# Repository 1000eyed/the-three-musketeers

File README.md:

# The three musketeers
A low(-ish) profile 3- or 4-row mechanical keyboard with a speaker supporting ortho and alpha stagger layouts, optional numpad, and optional 3 function keys.

## About

The three musketeers is a mechanical keyboard powered by RP2040 Zero development board. It is designed with optional clusters in mind, which you can either use or break away. Here are some particulars:

- Designed to support either KS-33B or Gateron low profile V3 switches. The PCB will accept the MX style switches too, but there is no case for these so far.
- I designed a couple of cases for this PCB, see below. All of them are low profile aimed on Gateron switches exclusively.
- Features KLJ-1102 speaker. I use it for announcing mod activation on keyboards with home row modifiers. You may use it for anything else per your liking, or not use it at all.
- Main cluster supports either ortho or alpha stagger layouts.
- There are multiple space row options, including 7U bar seesaw mount.
- No stabilizers!

## How to build one

> [!IMPORTANT]
> If you will be chopping the function column off the PCB, make sure this trace remains intact. Otherwise you will have to bridge it.
> 

#### Part list
| #     | name                 | comments                                  |
|-------|----------------------|-------------------------------------------|
| 1     | Main PCB             | Order at fabricator of your choice        |
| 1     | Case                 | See below                                 |
| 1     | RP2040 Zero          |                                           |
| 36-56 | Switches             | Gateron low profile KS-33b or v3          |
| 36-56 | Diodes               | SOD-123                                   |
| 36-56 | Keycaps              | MX-compatible                             |
| 4     | Rubber bump-ons      | 10mm                                      |
| 16    | Magnets              | Cylinder 1x5mm                            |
| 1     | Optional Speaker     | KLJ-1102 (https://keeb.supply/products/piezo-buzzer)  |

### 3D-printed cases

All these cases are printed in SLA by JLC. They turned out for me half-decent, and you may face warpage of longer parts. The assembly is straight-forward:

- Solder the sockets to the PCB and the pins to the controller.
- Solder the speaker of you have it.
- Mount the corner switches to the upper case part and solder them to the PCB. The PCB should seat flush to the integrated case.
- Mount and solder all other switches.
- Mount the controller onto the PCB.

Done!

### Concrete case

A successful attempt of a concrete case was made! I used MOBY DUR furniture concrete mixture, which turned out sturdy and was easy to demould, but required sanding (https://www.moertelshop.com/buy-white-grout-for-concrete-furniture-cheaply-5.html). You may or may not get better results with liquid floor mixtures.

The assembly consists of a concrete case and plate insert. The plate is soldered together with the PCB as with the 3D-printed cases, and then inserted into the case. It should be held inside firmly with friction.

- Print out the negative mould in PLA.
- Pour the concrete into the mold, make sure it sets level.
- When it sets, carefully demould with hot air gun. Try aiming at the mould rather than at the concrete directly.
- Repair any damage you made along the way.
- If you find this appealing, you same sand the case. Make sure not to sand the internal cavities!

### Aluminium case (handwire)

This version does not use the PCB at all, and thus is not directly connected to the The three musketeers project. However it was designed in the same wave of inspiration as everything else, so I figured it belongs here too. 

> [!NOTE]
> I used Kailh Element switches for this project. If you want to use different ones, check their plate footprint and adjust accordingly.

#### Part list
| #     | name                 | comments                                  |
|-------|----------------------|-------------------------------------------|
| 1     | Main case            | Order at fabricator of your choice        |
| 1     | Plate                | I printed out in PETG                     |
| 1     | MCU insert           | I printed out in PETG. Avoid brittle materials.                    |
| 1     | RP2040 Zero          |                                           |
| 36    | Switches             | Kailh Element                             |
| 36    | Diodes               |                                           |
| 36    | Keycaps              | MX-compatible                             |
| 4     | Rubber bump-ons      | 10mm                                      |
| 6     | M3 hex socket screws | 5 or 6 mm will do                               |
| 1     | Optional Speaker     | KLJ-1102 (https://keeb.supply/products/piezo-buzzer)  |

- Solder the switches to the plate with diodes like usual.
- Hook up the matrix to applicable pins on the controller.
- Clip in the controller into the controller insert.
- Clip the insert into the aluminim case.
- Screw the plate to the case while carefully laying out the wires. 

## Firmware

I don't provide firmware to this keyboard for now. For those wishing to compile their own, see the rows and columns references in the pcb schematic.

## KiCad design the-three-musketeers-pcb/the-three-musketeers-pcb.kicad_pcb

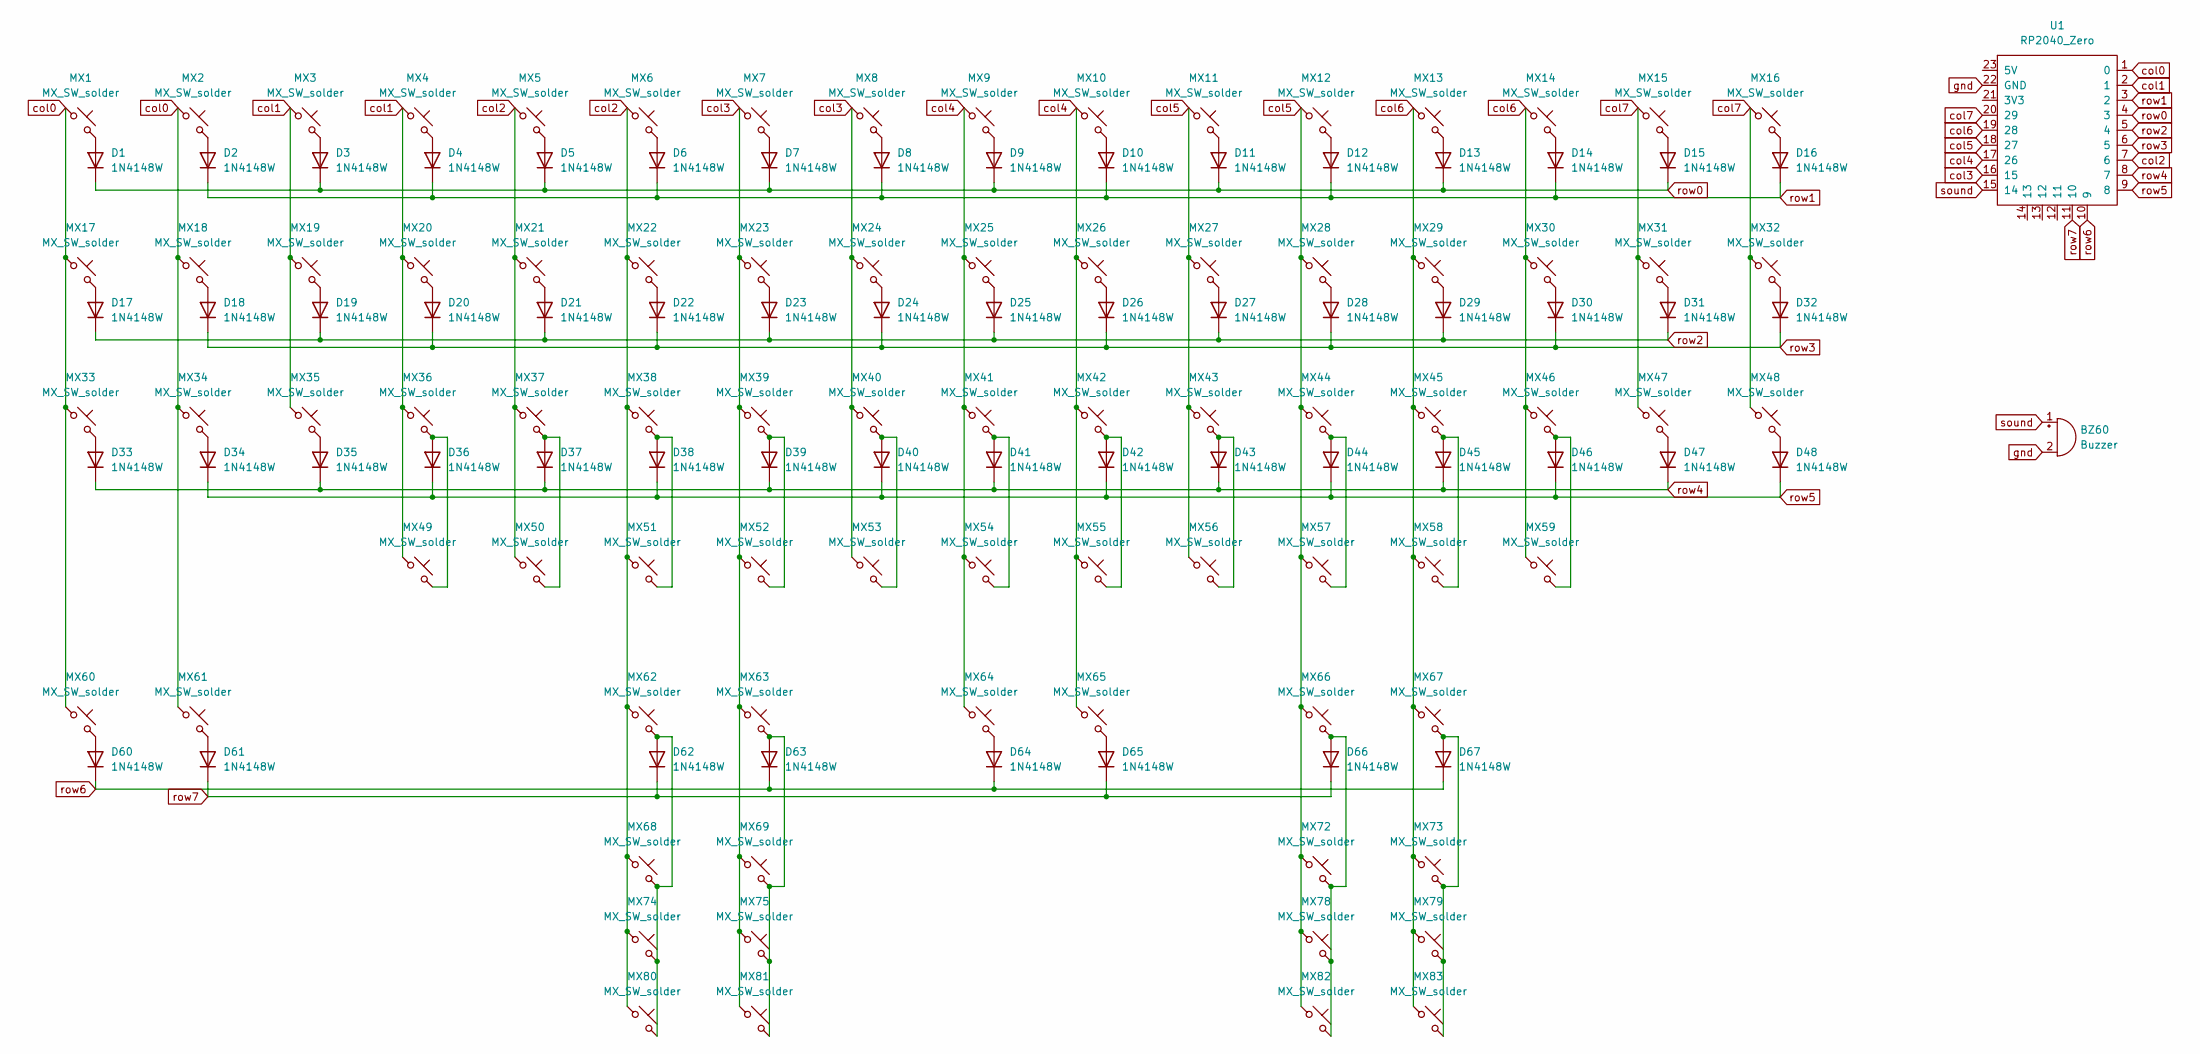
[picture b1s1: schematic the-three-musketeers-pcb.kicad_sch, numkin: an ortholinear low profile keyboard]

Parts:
BZ60: Buzzer; KLJ-1102
D1, D2, D3, D4, D5, D6, D7, D8, D9, D10, D11, D12, D13, D14, D15, D16, D17, D18, D19, D20, D21, D22, D23, D24, D25, D26, D27, D28, D29, D30, D31, D32, D33, D34, D35, D36, D37, D38, D39, D40, D41, D42, D43, D44, D45, D46, D47, D48, D60, D61, D62, D63, D64, D65, D66, D67: 1N4148W; Diode_SOD-123
MX1, MX2, MX3, MX4, MX5, MX6, MX7, MX8, MX9, MX10, MX11, MX12, MX13, MX14, MX15, MX16, MX17, MX18, MX19, MX20, MX21, MX22, MX23, MX24, MX25, MX26, MX27, MX28, MX29, MX30, MX31, MX32, MX33, MX34, MX35, MX36, MX37, MX38, MX39, MX40, MX41, MX42, MX43, MX44, MX45, MX46, MX47, MX48, MX49, MX50, MX51, MX52, MX53, MX54, MX55, MX56, MX57, MX58, MX59, MX60, MX61, MX62, MX63, MX64, MX65, MX66, MX67, MX68, MX69, MX72, MX73, MX74, MX75, MX78, MX79, MX80, MX81, MX82, MX83: MX_SW_solder; SW_MX+GLP_1u
U1: RP2040_Zero

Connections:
unnamed: D1.2 (A), MX1.2
unnamed: D2.2 (A), MX2.2
unnamed: D3.2 (A), MX3.2
unnamed: D4.2 (A), MX4.2
unnamed: D5.2 (A), MX5.2
unnamed: D6.2 (A), MX6.2
unnamed: D7.2 (A), MX7.2
unnamed: D8.2 (A), MX8.2
unnamed: D9.2 (A), MX9.2
unnamed: D10.2 (A), MX10.2
unnamed: D11.2 (A), MX11.2
unnamed: D12.2 (A), MX12.2
unnamed: D13.2 (A), MX13.2
unnamed: D14.2 (A), MX14.2
unnamed: D15.2 (A), MX15.2
unnamed: D16.2 (A), MX16.2
unnamed: D17.2 (A), MX17.2
unnamed: D18.2 (A), MX18.2
unnamed: D19.2 (A), MX19.2
unnamed: D20.2 (A), MX20.2
unnamed: D21.2 (A), MX21.2
unnamed: D22.2 (A), MX22.2
unnamed: D23.2 (A), MX23.2
unnamed: D24.2 (A), MX24.2
unnamed: D25.2 (A), MX25.2
unnamed: D26.2 (A), MX26.2
unnamed: D27.2 (A), MX27.2
unnamed: D28.2 (A), MX28.2
unnamed: D29.2 (A), MX29.2
unnamed: D30.2 (A), MX30.2
unnamed: D31.2 (A), MX31.2
unnamed: D32.2 (A), MX32.2
unnamed: D33.2 (A), MX33.2
unnamed: D34.2 (A), MX34.2
unnamed: D35.2 (A), MX35.2
unnamed: D36.2 (A), MX36.2, MX49.2
unnamed: D37.2 (A), MX37.2, MX50.2
unnamed: D38.2 (A), MX38.2, MX51.2
unnamed: D39.2 (A), MX39.2, MX52.2
unnamed: D40.2 (A), MX40.2, MX53.2
unnamed: D41.2 (A), MX41.2, MX54.2
unnamed: D42.2 (A), MX42.2, MX55.2
unnamed: D43.2 (A), MX43.2, MX56.2
unnamed: D44.2 (A), MX44.2, MX57.2
unnamed: D45.2 (A), MX45.2, MX58.2
unnamed: D46.2 (A), MX46.2, MX59.2
unnamed: D47.2 (A), MX47.2
unnamed: D48.2 (A), MX48.2
unnamed: D60.2 (A), MX60.2
unnamed: D61.2 (A), MX61.2
unnamed: D62.2 (A), MX62.2, MX68.2, MX74.2, MX80.2
unnamed: D63.2 (A), MX63.2, MX69.2, MX75.2, MX81.2
unnamed: D64.2 (A), MX64.2
unnamed: D65.2 (A), MX65.2
unnamed: D66.2 (A), MX66.2, MX72.2, MX78.2, MX82.2
unnamed: D67.2 (A), MX67.2, MX73.2, MX79.2, MX83.2
col0: MX1.1, MX2.1, MX17.1, MX18.1, MX33.1, MX34.1, MX60.1, MX61.1, U1.1 (0)
col1: MX3.1, MX4.1, MX19.1, MX20.1, MX35.1, MX36.1, MX49.1, U1.2 (1)
col2: MX5.1, MX6.1, MX21.1, MX22.1, MX37.1, MX38.1, MX50.1, MX51.1, MX62.1, MX68.1, MX74.1, MX80.1, U1.7 (6)
col3: MX7.1, MX8.1, MX23.1, MX24.1, MX39.1, MX40.1, MX52.1, MX53.1, MX63.1, MX69.1, MX75.1, MX81.1, U1.16 (15)
col4: MX9.1, MX10.1, MX25.1, MX26.1, MX41.1, MX42.1, MX54.1, MX55.1, MX64.1, MX65.1, U1.17 (26)
col5: MX11.1, MX12.1, MX27.1, MX28.1, MX43.1, MX44.1, MX56.1, MX57.1, MX66.1, MX72.1, MX78.1, MX82.1, U1.18 (27)
col6: MX13.1, MX14.1, MX29.1, MX30.1, MX45.1, MX46.1, MX58.1, MX59.1, MX67.1, MX73.1, MX79.1, MX83.1, U1.19 (28)
col7: MX15.1, MX16.1, MX31.1, MX32.1, MX47.1, MX48.1, U1.20 (29)
gnd: BZ60.2 (-), U1.22 (GND)
row0: D1.1 (K), D3.1 (K), D5.1 (K), D7.1 (K), D9.1 (K), D11.1 (K), D13.1 (K), D15.1 (K), U1.4 (3)
row1: D2.1 (K), D4.1 (K), D6.1 (K), D8.1 (K), D10.1 (K), D12.1 (K), D14.1 (K), D16.1 (K), U1.3 (2)
row2: D17.1 (K), D19.1 (K), D21.1 (K), D23.1 (K), D25.1 (K), D27.1 (K), D29.1 (K), D31.1 (K), U1.5 (4)
row3: D18.1 (K), D20.1 (K), D22.1 (K), D24.1 (K), D26.1 (K), D28.1 (K), D30.1 (K), D32.1 (K), U1.6 (5)
row4: D33.1 (K), D35.1 (K), D37.1 (K), D39.1 (K), D41.1 (K), D43.1 (K), D45.1 (K), D47.1 (K), U1.8 (7)
row5: D34.1 (K), D36.1 (K), D38.1 (K), D40.1 (K), D42.1 (K), D44.1 (K), D46.1 (K), D48.1 (K), U1.9 (8)
row6: D60.1 (K), D63.1 (K), D64.1 (K), D67.1 (K), U1.10 (9)
row7: D61.1 (K), D62.1 (K), D65.1 (K), D66.1 (K), U1.11 (10)
sound: BZ60.1 (+), U1.15 (14)

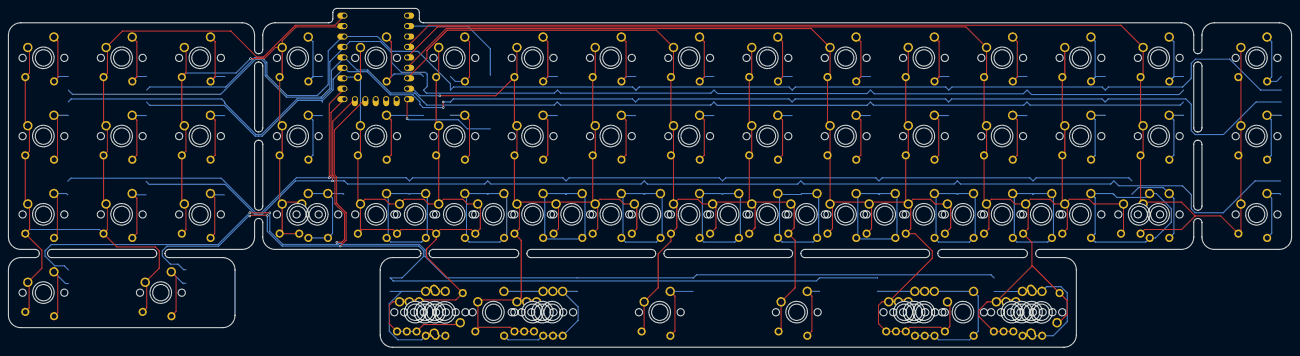
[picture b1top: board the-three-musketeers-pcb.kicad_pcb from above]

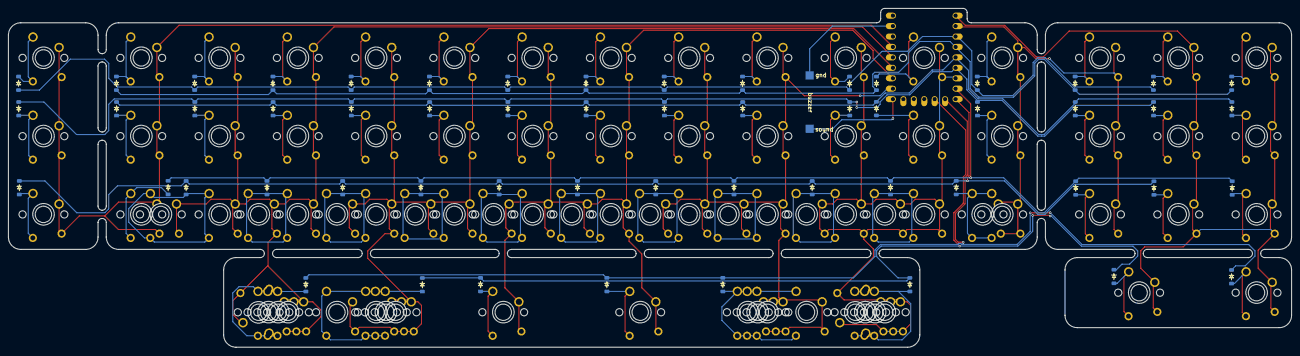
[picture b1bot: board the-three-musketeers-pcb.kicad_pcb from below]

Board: 2 copper layers, 312.3 x 82.5 mm, 137 parts (58 on the bottom side), 74 nets.

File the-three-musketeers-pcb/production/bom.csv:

Designator,Footprint,Quantity,Value,LCSC Part #
BZ60,KLJ-1102,1,Buzzer,
"D1, D10, D11, D12, D13, D14, D15, D16, D17, D18, D19, D2, D20, D21, D22, D23, D24, D25, D26, D27, D28, D29, D3, D30, D31, D32, D33, D34, D35, D36, D37, D38, D39, D4, D40, D41, D42, D43, D44, D45, D46, D47, D48, D5, D6, D60, D61, D62, D63, D64, D65, D66, D67, D7, D8, D9",Diode_SOD-123,56,1N4148W,
"MX1, MX10, MX11, MX12, MX13, MX14, MX15, MX16, MX17, MX18, MX19, MX2, MX20, MX21, MX22, MX23, MX24, MX25, MX26, MX27, MX28, MX29, MX3, MX30, MX31, MX32, MX33, MX34, MX35, MX36, MX37, MX38, MX39, MX4, MX40, MX41, MX42, MX43, MX44, MX45, MX46, MX47, MX48, MX49, MX5, MX50, MX51, MX52, MX53, MX54, MX55, MX56, MX57, MX58, MX59, MX6, MX60, MX61, MX62, MX63, MX64, MX65, MX66, MX67, MX68, MX69, MX7, MX72, MX73, MX74, MX75, MX78, MX79, MX8, MX80, MX81, MX82, MX83, MX9",SW_MX+GLP_1u,79,MX_SW_solder,
U1,RP2040_Zero,1,RP2040_Zero,

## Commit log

2025-09-29 Fix capitalization in project title
2025-09-29 add case files
2025-09-29 Update keyboard description in README
2025-09-29 add photos
2025-09-29 Add image to README for visual reference
2025-09-29 Enhance README with keyboard details and specifications
    Added an 'About' section detailing the keyboard features and specifications.
2025-09-29 Fix grammatical errors in README.md
2025-09-29 Update README with layout and stabilizer information
    Added details about layout options and stabilizers.
2025-09-29 add kle info
